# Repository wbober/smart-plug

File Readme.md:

Rime-Plug
=========

Rime plug is a smart plug with a relay, energy monitor, and 802.15.4 radio.

Hardware
--------
* deRFmega128 radio module (ATmega128RFA1 with a chip antenna)
* ADE7757 energy monitor
* 16A relay

Sofware (Todo)
--------------
* Contiki OS
* Rime network stack

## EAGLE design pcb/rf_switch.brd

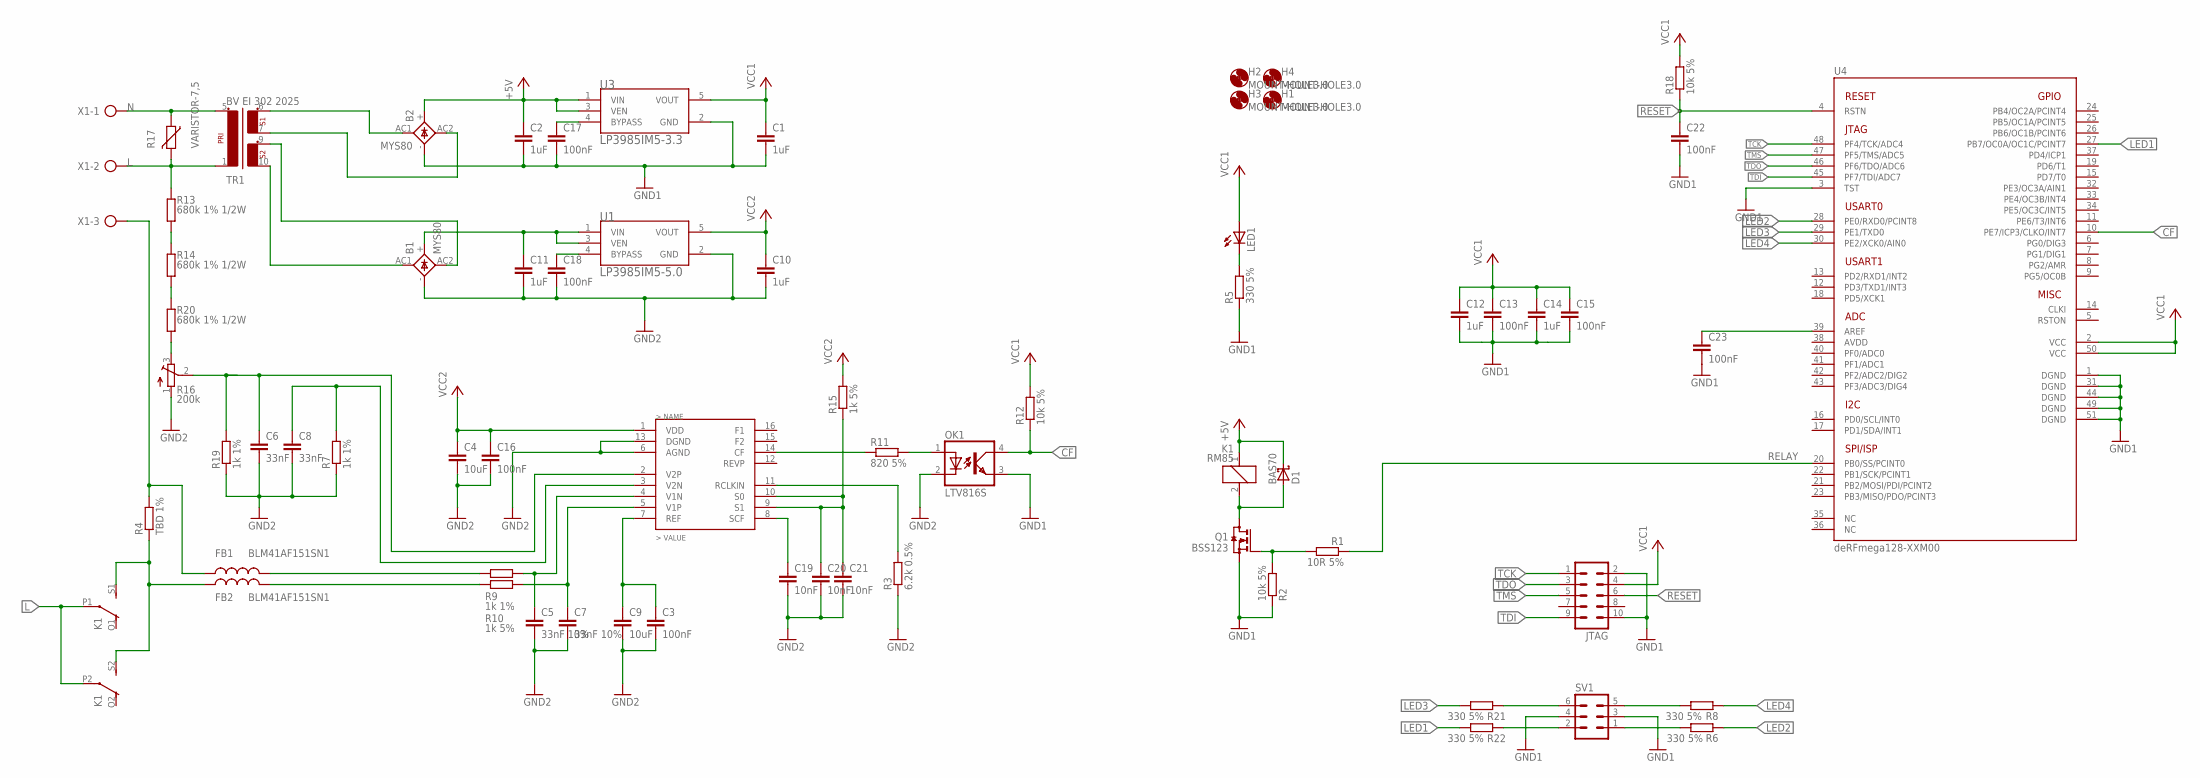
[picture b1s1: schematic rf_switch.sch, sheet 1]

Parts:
B1, B2: MYS80; MICRODIL
C1, C2, C10, C11, C12, C14: 1uF; C0603
C3, C13, C15, C16, C17, C18, C22, C23: 100nF; C0603
C4, C9: 10uF; C0805
C5, C7: 33nF 10%; C0805
C6, C8: 33nF; C0603
C19, C20, C21: 10nF; C0603
D1: BAS70; SOT23
FB1, FB2: BLM41AF151SN1; 1806
H1, H2, H3, H4: MOUNT-HOLE3.0; 3,0
JTAG: MA05-2
K1: RM85; F4052
LED1: LEDSML0603; SML0603
OK1: LTV816S; SMD4
Q1: BSS123; SOT23
R1: 10R 5%; R0603
R2, R12, R18: 10k 5%; R0603
R3: 6.2k 0.5%; R0603
R4: TBD 1%; R1206
R5, R6, R8, R21, R22: 330 5%; R0603
R7, R19: 1k 1%; R0603
R9: 1k 1%; R1206
R10: 1k 5%; R1206
R11: 820 5%; R0603
R13, R14, R20: 680k 1% 1/2W; R1206
R15: 1k 5%; R0603
R16: 200k; 3223W
R17: VARISTOR-7,5; R-7,5
SV1: MA03-2
TR1: BV EI 302 2025; EI30-2
U1: LP3985IM5-5.0; SOT95P300X120-5N
U2: ADE7757; SOIC-16
U3: LP3985IM5-3.3; SOT95P300X120-5N
U4: DERFMEGA128-XXM00; A-M00
X1: AK500/3

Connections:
+5V: B2.+, C2.1, D1.3 (C), K1.1, U3.1 (VIN), U3.3 (VEN)
CF: OK1.4 (COL), R12.1, U4.10 (PE7/ICP3/CLKO/INT7)
CF1: C20.1, C21.1, R15.1, U2.9 (S1), U2.10 (S0)
COMMON: FB1.P$1 (1), R4.2, X1.3
GND1: B2.-, C1.2, C2.2, C12.2, C13.2, C14.2, C15.2, C17.2, C22.2, C23.2, JTAG.2, JTAG.10, OK1.3 (EMIT), Q1.2 (S), R2.1, R5.1, SV1.3, SV1.4, U3.2 (GND), U4.1 (DGND), U4.3 (TST), U4.31 (DGND), U4.44 (DGND), U4.49 (DGND), U4.51 (DGND)
GND2: B1.-, C3.2, C4.2, C5.2, C6.2, C7.2, C8.2, C9.2, C10.2, C11.2, C16.2, C18.2, C19.2, C20.2, C21.2, OK1.2 (C), R3.1, R7.1, R16.1 (A), R19.1, U1.2 (GND), U2.6 (AGND), U2.13 (DGND)
L: K1.P1, K1.P2, R13.1, R17.2, TR1.1, X1.2
LED1: R22.1, U4.27 (PB7/OC0A/OC1C/PCINT7)
LED2: R6.1, U4.28 (PE0/RXD0/PCINT8)
LED3: R21.1, U4.29 (PE1/TXD0)
LED4: R8.1, U4.30 (PE2/XCK0/AIN0)
N: R17.1, TR1.5 (2), X1.1
unnamed: Q1.1 (G), R1.2, R2.2
unnamed: B1.+, C11.1, U1.1 (VIN), U1.3 (VEN)
unnamed: R11.1, U2.14 (CF)
unnamed: R13.2, R14.1
unnamed: OK1.1 (A), R11.2
unnamed: D1.1 (A), K1.2, Q1.3 (D)
unnamed: R14.2, R20.1
unnamed: R3.2, U2.11 (RCLKIN)
unnamed: C19.1, U2.8 (SCF)
unnamed: FB1.P$2 (2), R9.1
unnamed: R16.3 (E), R20.2
unnamed: C3.1, C9.1, U2.7 (REF)
unnamed: B2.AC2, TR1.7 (4)
unnamed: C23.1, U4.39 (AREF)
unnamed: FB2.P$1 (1), K1.S1 (S), K1.S2 (S), R4.1
unnamed: FB2.P$2 (2), R10.1
unnamed: B1.AC1, TR1.10 (6)
unnamed: B1.AC2, TR1.9 (5)
unnamed: R8.2, SV1.5
unnamed: B2.AC1, TR1.6 (3)
unnamed: LED1.C, R5.2
unnamed: C17.1, U3.4 (BYPASS)
unnamed: C18.1, U1.4 (BYPASS)
unnamed: R21.2, SV1.6
unnamed: R22.2, SV1.2
unnamed: R6.2, SV1.1
RELAY: R1.1, U4.20 (PB0/SS/PCINT0)
RESET: C22.1, JTAG.6, R18.1, U4.4 (RSTN)
TCK: JTAG.1, U4.48 (PF4/TCK/ADC4)
TDI: JTAG.9, U4.45 (PF7/TDI/ADC7)
TDO: JTAG.3, U4.46 (PF6/TDO/ADC6)
TMS: JTAG.5, U4.47 (PF5/TMS/ADC5)
V1N: C5.1, R9.2, U2.4 (V1N)
V1P: C7.1, R10.2, U2.5 (V1P)
V2N: C8.1, R7.2, U2.3 (V2N)
V2P: C6.1, R16.2 (S), R19.2, U2.2 (V2P)
VCC1: C1.1, C12.1, C13.1, C14.1, C15.1, JTAG.4, LED1.A, R12.2, R18.2, U3.5 (VOUT), U4.2 (VCC), U4.50 (VCC)
VCC2: C4.1, C10.1, C16.1, R15.2, U1.5 (VOUT), U2.1 (VDD)

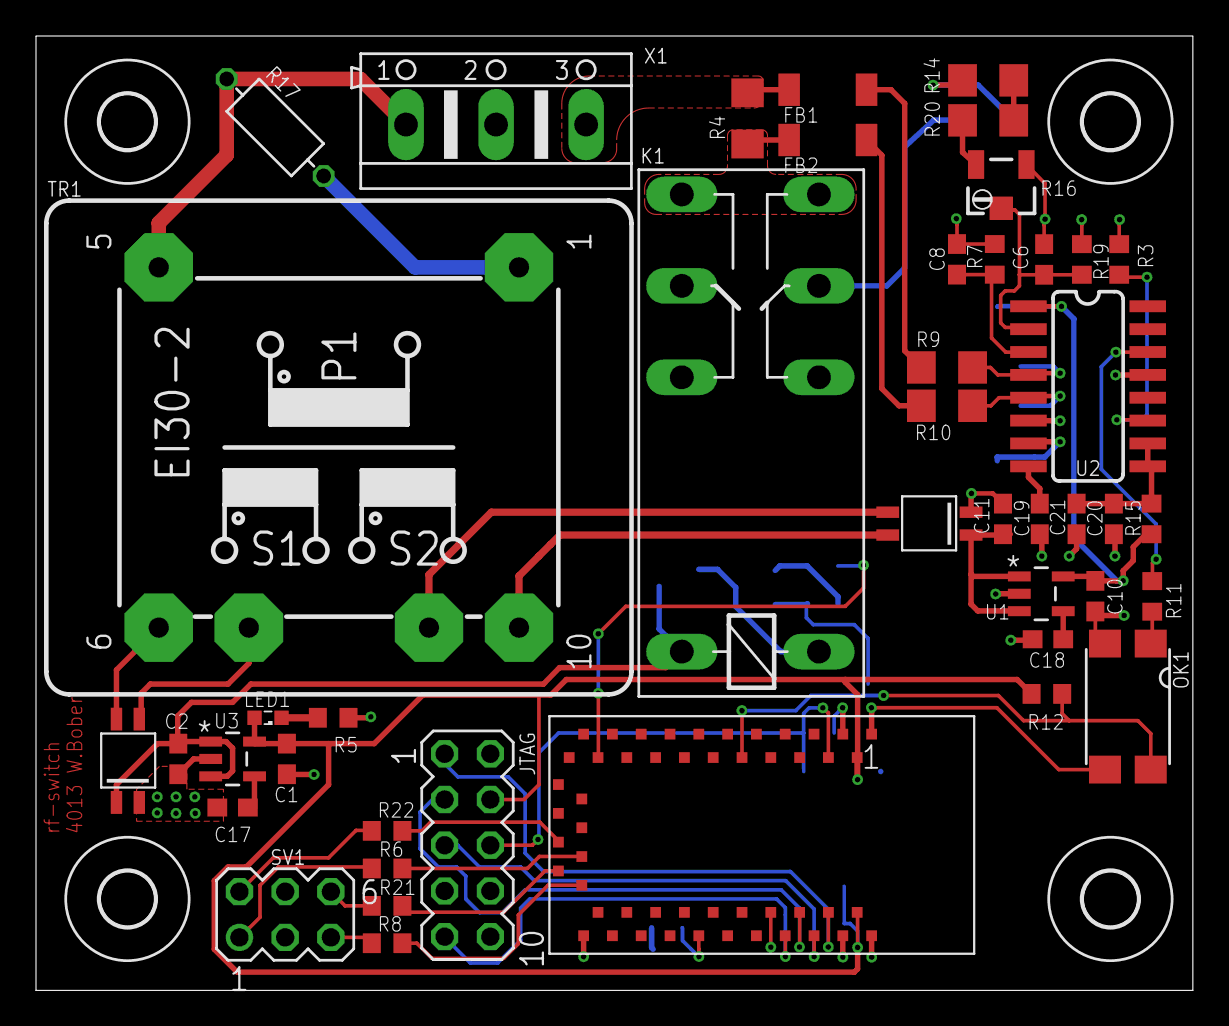
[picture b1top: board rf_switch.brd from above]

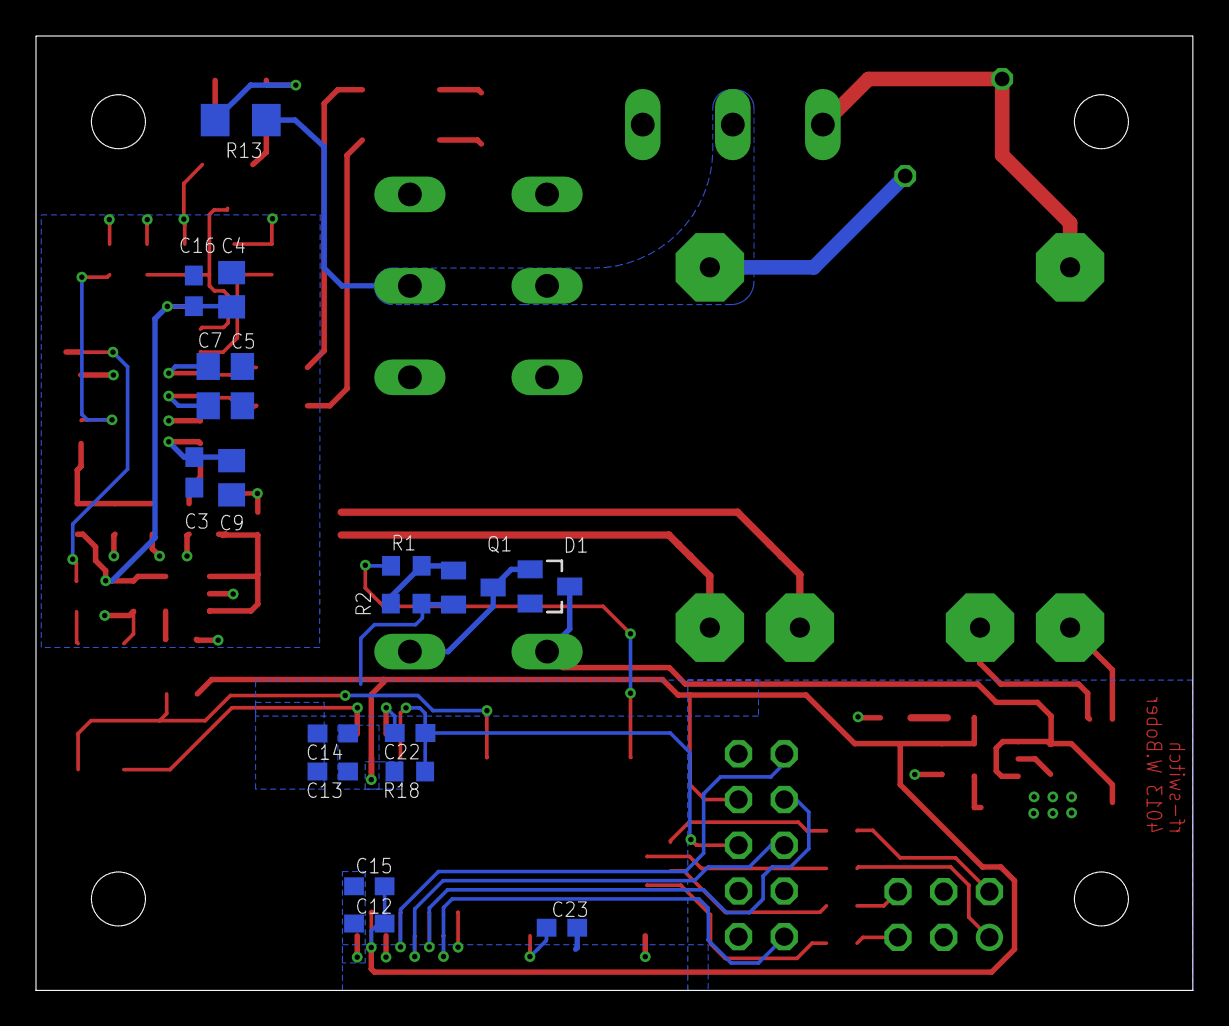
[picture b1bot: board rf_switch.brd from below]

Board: 4 copper layers, 64.3 x 53.0 mm, 66 parts (18 on the bottom side), 50 nets.

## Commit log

2014-11-27 Schematics and pcb.
2014-11-27 Added gitignore
2014-11-27 Added fabrication files
2014-11-27 Added Readme.md
2014-12-01 Eclipse project files
2014-12-01 Source files
2014-12-01 Moved source code to firmware folder
2014-12-01 Added files to git ignore
2014-12-09 Cleanup
